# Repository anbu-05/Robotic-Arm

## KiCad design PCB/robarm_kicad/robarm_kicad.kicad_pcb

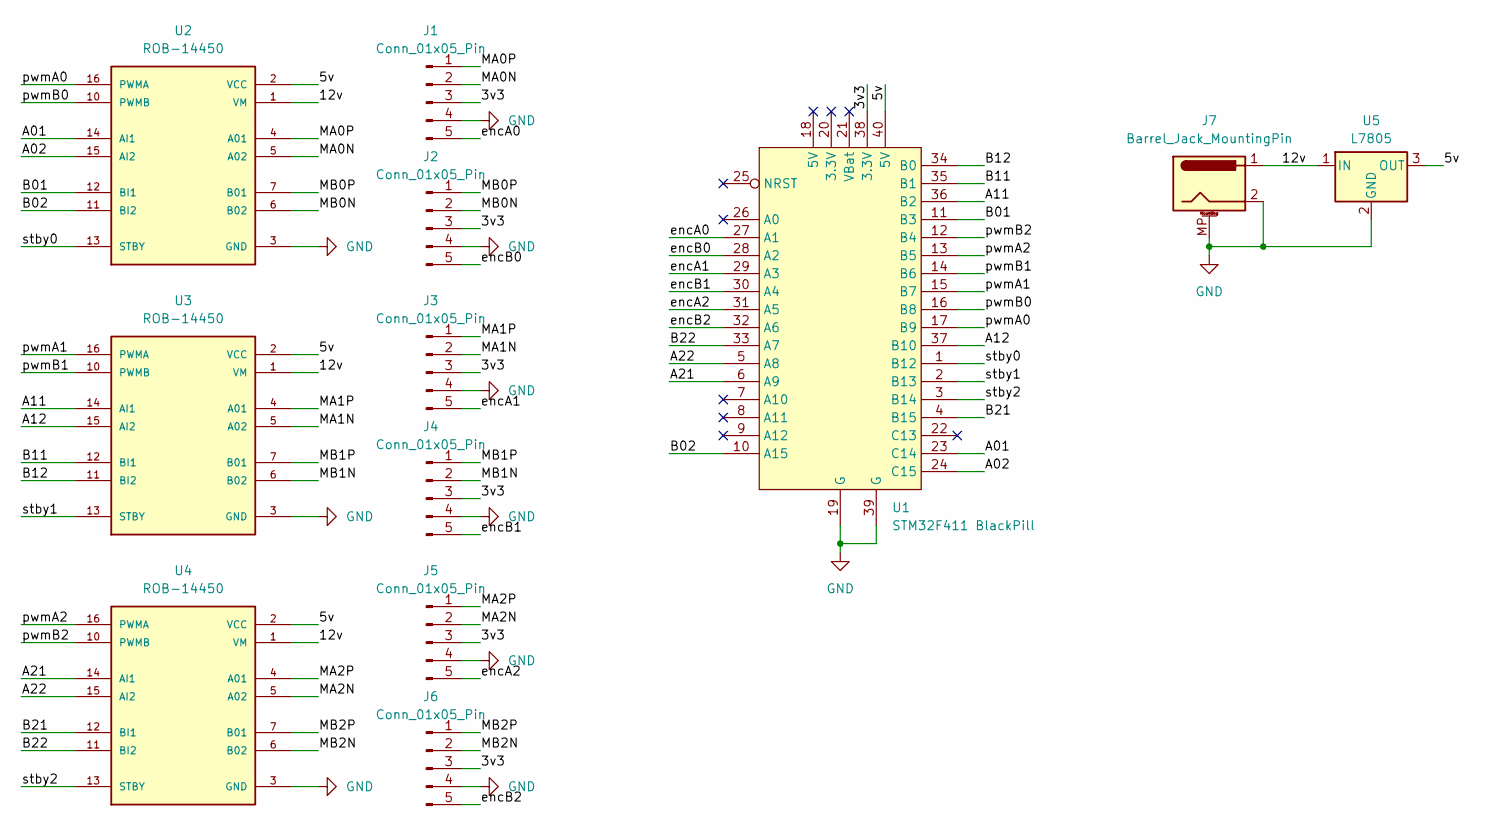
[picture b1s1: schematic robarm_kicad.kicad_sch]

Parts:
J1, J2, J3, J4, J5, J6: Conn_01x05_Pin; JST_XH_B5B-XH-A_1x05_P2.50mm_Vertical
J7: Barrel_Jack_MountingPin; BarrelJack_Horizontal
U1: STM32F411 BlackPill; STM32F411_Black_Pill
U2, U3, U4: ROB-14450; MODULE_ROB-14450; PARTREV 11-13-17
U5: L7805; TO-220-3_Horizontal_TabDown

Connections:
/3v3: J1.3, J2.3, J3.3, J4.3, J5.3, J6.3, U1.38 (3.3V)
/5v: U1.40 (5V), U2.2 (VCC), U3.2 (VCC), U4.2 (VCC), U5.3 (OUT)
/12v: J7.1, U2.1 (VM), U3.1 (VM), U4.1 (VM), U5.1 (IN)
/A01: U1.23 (C14), U2.14 (AI1)
/A02: U1.24 (C15), U2.15 (AI2)
/A11: U1.36 (B2), U3.14 (AI1)
/A12: U1.37 (B10), U3.15 (AI2)
/A21: U1.6 (A9), U4.14 (AI1)
/A22: U1.5 (A8), U4.15 (AI2)
/B01: U1.11 (B3), U2.12 (BI1)
/B02: U1.10 (A15), U2.11 (BI2)
/B11: U1.35 (B1), U3.12 (BI1)
/B12: U1.34 (B0), U3.11 (BI2)
/B21: U1.4 (B15), U4.12 (BI1)
/B22: U1.33 (A7), U4.11 (BI2)
/MA0N: J1.2, U2.5 (A02)
/MA0P: J1.1, U2.4 (A01)
/MA1N: J3.2, U3.5 (A02)
/MA1P: J3.1, U3.4 (A01)
/MA2N: J5.2, U4.5 (A02)
/MA2P: J5.1, U4.4 (A01)
/MB0N: J2.2, U2.6 (B02)
/MB0P: J2.1, U2.7 (B01)
/MB1N: J4.2, U3.6 (B02)
/MB1P: J4.1, U3.7 (B01)
/MB2N: J6.2, U4.6 (B02)
/MB2P: J6.1, U4.7 (B01)
/encA0: J1.5, U1.27 (A1)
/encA1: J3.5, U1.29 (A3)
/encA2: J5.5, U1.31 (A5)
/encB0: J2.5, U1.28 (A2)
/encB1: J4.5, U1.30 (A4)
/encB2: J6.5, U1.32 (A6)
/pwmA0: U1.17 (B9), U2.16 (PWMA)
/pwmA1: U1.15 (B7), U3.16 (PWMA)
/pwmA2: U1.13 (B5), U4.16 (PWMA)
/pwmB0: U1.16 (B8), U2.10 (PWMB)
/pwmB1: U1.14 (B6), U3.10 (PWMB)
/pwmB2: U1.12 (B4), U4.10 (PWMB)
/stby0: U1.1 (B12), U2.13 (STBY)
/stby1: U1.2 (B13), U3.13 (STBY)
/stby2: U1.3 (B14), U4.13 (STBY)
GND: J1.4, J2.4, J3.4, J4.4, J5.4, J6.4, J7.2, J7.MP (MountPin), U1.19 (G), U1.39 (G), U2.3 (GND), U2.8 (GND), U2.9 (GND), U3.3 (GND), U3.8 (GND), U3.9 (GND), U4.3 (GND), U4.8 (GND), U4.9 (GND), U5.2 (GND)

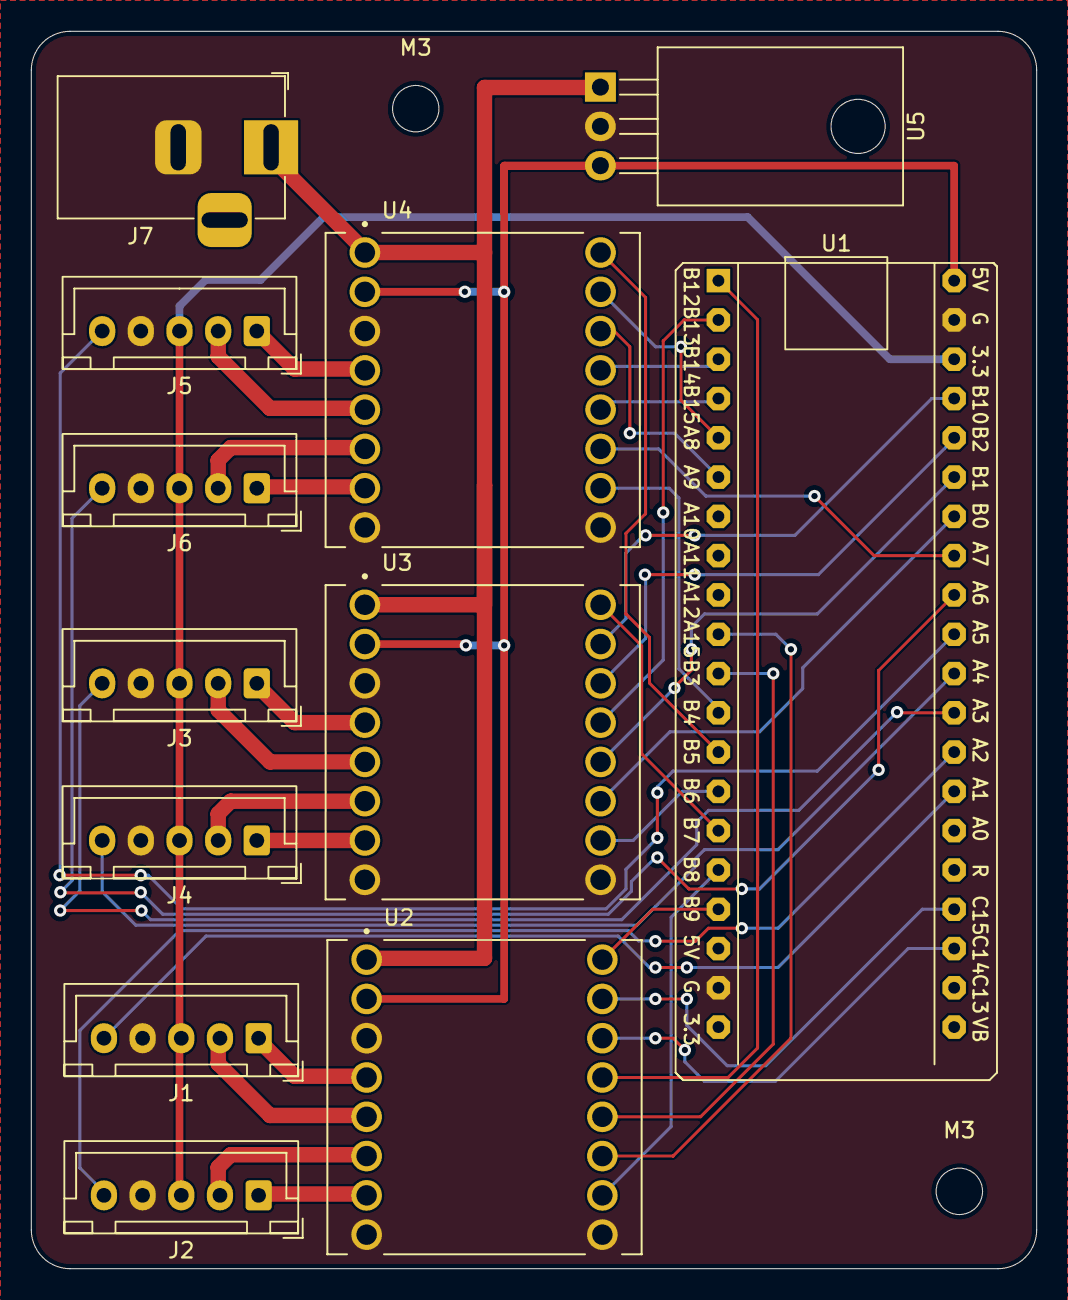
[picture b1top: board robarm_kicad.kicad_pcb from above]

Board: 2 copper layers, 65.0 x 80.0 mm, 14 parts (0 on the bottom side), 43 nets.

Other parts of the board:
M3, M3#2: MountingHole_3mm

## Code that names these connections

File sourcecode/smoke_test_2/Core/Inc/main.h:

/* USER CODE BEGIN Header */
/**
  ******************************************************************************
  * @file           : main.h
  * @brief          : Header for main.c file.
  *                   This file contains the common defines of the application.
  ******************************************************************************
  * @attention
  *
  * Copyright (c) 2026 STMicroelectronics.
  * All rights reserved.
  *
  * This software is licensed under terms that can be found in the LICENSE file
  * in the root directory of this software component.
  * If no LICENSE file comes with this software, it is provided AS-IS.
  *
  ******************************************************************************
  */
/* USER CODE END Header */

/* Define to prevent recursive inclusion -------------------------------------*/
#ifndef __MAIN_H
#define __MAIN_H

#ifdef __cplusplus
extern "C" {
#endif

/* Includes ------------------------------------------------------------------*/
#include "stm32f4xx_hal.h"

/* Private includes ----------------------------------------------------------*/
/* USER CODE BEGIN Includes */

/* USER CODE END Includes */

/* Exported types ------------------------------------------------------------*/
/* USER CODE BEGIN ET */

/* USER CODE END ET */

/* Exported constants --------------------------------------------------------*/
/* USER CODE BEGIN EC */

/* USER CODE END EC */

/* Exported macro ------------------------------------------------------------*/
/* USER CODE BEGIN EM */

/* USER CODE END EM */

void HAL_TIM_MspPostInit(TIM_HandleTypeDef *htim);

/* Exported functions prototypes ---------------------------------------------*/
void Error_Handler(void);

/* USER CODE BEGIN EFP */

/* USER CODE END EFP */

/* Private defines -----------------------------------------------------------*/
#define usr_led_Pin GPIO_PIN_13
#define usr_led_GPIO_Port GPIOC
#define A01_Pin GPIO_PIN_14
#define A01_GPIO_Port GPIOC
#define A02_Pin GPIO_PIN_15
#define A02_GPIO_Port GPIOC
#define key_Pin GPIO_PIN_0
#define key_GPIO_Port GPIOA
#define key_EXTI_IRQn EXTI0_IRQn
#define encA0_Pin GPIO_PIN_1
#define encA0_GPIO_Port GPIOA
#define encB0_Pin GPIO_PIN_2
#define encB0_GPIO_Port GPIOA
#define encA1_Pin GPIO_PIN_3
#define encA1_GPIO_Port GPIOA
#define encB1_Pin GPIO_PIN_4
#define encB1_GPIO_Port GPIOA
#define encA2_Pin GPIO_PIN_5
#define encA2_GPIO_Port GPIOA
#define encB2_Pin GPIO_PIN_6
#define encB2_GPIO_Port GPIOA
#define B21_Pin GPIO_PIN_7
#define B21_GPIO_Port GPIOA
#define B12_Pin GPIO_PIN_0
#define B12_GPIO_Port GPIOB
#define B11_Pin GPIO_PIN_1
#define B11_GPIO_Port GPIOB
#define A11_Pin GPIO_PIN_2
#define A11_GPIO_Port GPIOB
#define A12_Pin GPIO_PIN_10
#define A12_GPIO_Port GPIOB
#define STBY0_Pin GPIO_PIN_12
#define STBY0_GPIO_Port GPIOB
#define STBY1_Pin GPIO_PIN_13
#define STBY1_GPIO_Port GPIOB
#define STBY2_Pin GPIO_PIN_14
#define STBY2_GPIO_Port GPIOB
#define B22_Pin GPIO_PIN_15
#define B22_GPIO_Port GPIOB
#define A22_Pin GPIO_PIN_8
#define A22_GPIO_Port GPIOA
#define A21_Pin GPIO_PIN_9
#define A21_GPIO_Port GPIOA
#define B01_Pin GPIO_PIN_15
#define B01_GPIO_Port GPIOA
#define B02_Pin GPIO_PIN_3
#define B02_GPIO_Port GPIOB
#define pwmB2_Pin GPIO_PIN_4
#define pwmB2_GPIO_Port GPIOB
#define pwmA2_Pin GPIO_PIN_5
#define pwmA2_GPIO_Port GPIOB
#define pwmB1_Pin GPIO_PIN_6
#define pwmB1_GPIO_Port GPIOB
#define pwmA1_Pin GPIO_PIN_7
#define pwmA1_GPIO_Port GPIOB
#define pwmB0_Pin GPIO_PIN_8
#define pwmB0_GPIO_Port GPIOB
#define pwmA0_Pin GPIO_PIN_9
#define pwmA0_GPIO_Port GPIOB

/* USER CODE BEGIN Private defines */

/* USER CODE END Private defines */

#ifdef __cplusplus
}
#endif

#endif /* __MAIN_H */

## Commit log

2026-04-17 got basic motor and pot control working on the elbow joint. some hardware issues on the wrist pitch.
2026-04-17 started work on homing sequence
2026-04-26 trying out vscode stm32cube
2026-04-26 created a motor struct, i can now receive usb rx data and parse it into motor pwm and direction values
2026-04-28 got the motor control working in ONE direction. the other direction is still not working. ADC still not working
2026-04-29 all 6 motor controls working. all 6 ADCs are being read properly. need now i just need to reduce noise and make ADCs values smooth. im working on a cli library tho, microrl
2026-04-29 got microrl integrated and working
2026-04-29 implemented ADC filtering
2026-04-29 updated readme. figured out some bugs
2026-04-30 fixed some bugs, figured out others
2026-04-30 fixed spike rejection bug
2026-04-30 the position control works now
2026-05-10 updated the firmware. created a python control driver -it's a webserver with controls to control this bot
2026-05-10 added position limits to firmware
2026-06-16 pushing all the code so far
2026-06-17 created a 2d kinematics visualizer
2026-06-18 visualizer working
